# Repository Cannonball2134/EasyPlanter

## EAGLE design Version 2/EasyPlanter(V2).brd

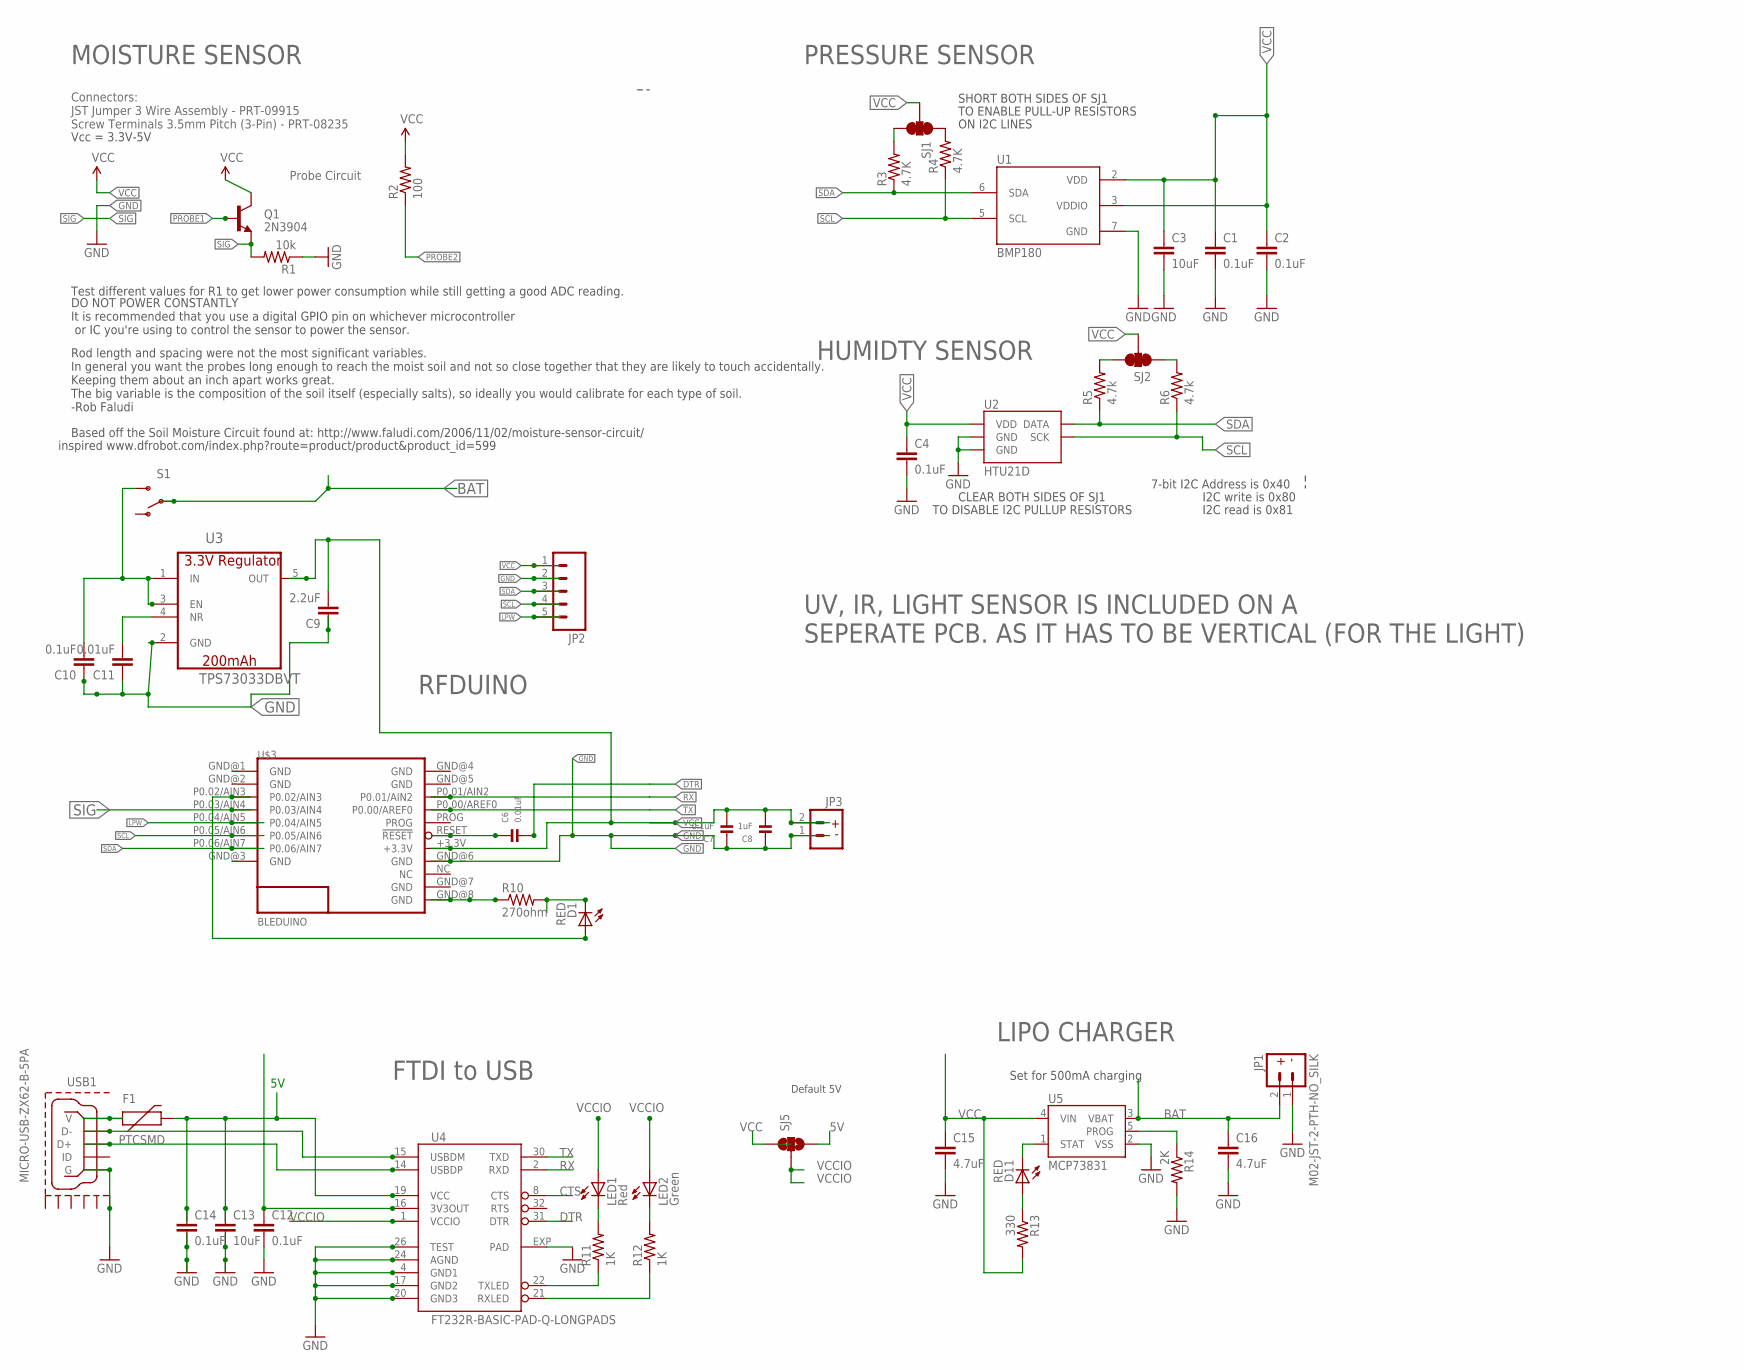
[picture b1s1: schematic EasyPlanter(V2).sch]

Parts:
C1, C2, C4: 0.1uF; 0603-CAP
C3: 10uF; 0603-CAP
C6: 0.01uF; 0402
C7: 0.1uF; 0402
C8: 1uF; 0402
C9: 2.2uF; 0402-CAP
C10, C12, C14: 0.1uF; 0402-CAP
C11: 0.01uF; 0402-CAP
C13: 10uF; 0402-CAP
C15, C16: 4.7uF; 0402-CAP
D1, D11: RED; LED-0603
F1: PTCSMD; PTC-1206
JP1, JP3: M02-JST-2-PTH-NO_SILK; JST-2-PTH-NS
JP2: M05PTH; 1X05
LED1: Red; LED-0603
LED2: Green; LED-0603
Q1: 2N3904; SOT23-3
R1: 10k; 0603-RES
R2: 100; 0603-RES
R3, R4: 4.7K; 0603-RES
R5, R6: 4.7k; 0603-RES
R10: 270ohm; 0402-RES
R11, R12: 1K; R0402
R13: 330; 0402-RES
R14: 2K; 0402-RES
S1: SWITCH-SPDT-SMD-A; SWITCH-SPST-SMD-A
SJ1, SJ2: SOLDERJUMPER_2WAYPASTE1&2&3; SJ_3_PASTE1&2&3
SJ5: SOLDERJUMPER_2WAY-LEFT-BRIDGED; SJ-3-LEFT
U1: BMP180
U2: HTU21D
U3: TPS73033DBVT; SOT95P290X145-5N
U4: FT232R-BASIC-PAD-Q-LONGPADS; QFN32-LONG
U5: MCP73831; SOT23-5
U$3: BLEDUINO
USB1: MICRO-USB-ZX62-B-5PA; ZX62-B-5PA

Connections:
5V: C13.1, C14.1, F1.2, SJ5.3, U4.19 (VCC)
BAT: C16.1, JP1.2, S1.2, U5.3 (VBAT)
BAT_INPUT: C10.2, S1.3 (S), U3.1 (IN), U3.3 (EN)
CTS: U4.8 (CTS)
DTR: C6.2, U4.31 (DTR)
GND: C1.2, C2.2, C3.2, C4.2, C7.1, C8.1, C9.1, C10.1, C11.1, C12.2, C13.2, C14.2, C15.2, C16.2, JP1.1, JP2.2, JP3.1, R1.1, R14.2, U1.7 (GND), U2.7 (GND), U2.GND, U3.2 (GND), U4.4 (GND1), U4.17 (GND2), U4.20 (GND3), U4.24 (AGND), U4.26 (TEST), U4.EXP (PAD), U5.2 (VSS), U$3.GND@6 (GND), USB1.5 (G), USB1.GND@6 (GND6)
GND1: USB1.GND@1 (GND1)
GND2: USB1.GND@2 (GND2)
GND3: USB1.GND@3 (GND3)
GND4: USB1.GND@4 (GND4)
GND5: USB1.GND@5 (GND5)
LPW: JP2.5, U$3.P0.04/AIN5
unnamed: R3.2, SJ1.3
unnamed: R4.2, SJ1.1
unnamed: R5.2, SJ2.3
unnamed: R6.2, SJ2.1
unnamed: C6.1, U$3.RESET (!RESET)
unnamed: D1.A, U$3.P0.02/AIN3
unnamed: C11.2, U3.4 (NR)
unnamed: U4.14 (USBDP), USB1.3 (D+)
unnamed: U4.15 (USBDM), USB1.2 (D-)
unnamed: R12.1, U4.21 (RXLED)
unnamed: R11.1, U4.22 (TXLED)
unnamed: F1.1, USB1.1 (V)
unnamed: LED1.C, R11.2
unnamed: LED2.C, R12.2
unnamed: D11.A, R13.1
unnamed: D1.C, R10.2
unnamed: R10.1, U$3.GND@8 (GND)
PROBE1: Q1.1 (B)
PROBE2: R2.1
PROG: R14.1, U5.5 (PROG)
RX: U4.2 (RXD), U$3.P0.01/AIN2
SCL: JP2.4, R4.1, R6.1, U1.5 (SCL), U2.SCK, U$3.P0.05/AIN6
SDA: JP2.3, R3.1, R5.1, U1.6 (SDA), U2.DATA, U$3.P0.06/AIN7
SIG: Q1.2 (E), R1.2, U$3.P0.03/AIN4
STAT: D11.C, U5.1 (STAT)
TX: U4.30 (TXD), U$3.P0.00/AREF0
VCC: C1.1, C2.1, C3.1, C4.1, C7.2, C8.2, C9.2, C12.1, C15.1, JP2.1, JP3.2, Q1.3 (C), R2.2, R13.2, SJ1.2, SJ2.2, SJ5.1, U1.2 (VDD), U1.3 (VDDIO), U2.VDD, U3.5 (OUT), U4.16 (3V3OUT), U5.4 (VIN), U$3.+3.3V
VCCIO: LED1.A, LED2.A, SJ5.2, U4.1 (VCCIO)

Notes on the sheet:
Test different values for R1 to get lower power consumption while still getting a good ADC reading.
Based off the Soil Moisture Circuit found at: http://www.faludi.com/2006/11/02/moisture-sensor-circuit/
Rod length and spacing were not the most significant variables. In general you want the probes long enough to reach the moist soil and not so close together that they are likely to touch accidentally. Keeping them about an inch apart works great. The big variable is the composition of the soil itse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
Connectors: JST Jumper 3 Wire Assembly - PRT-09915 Screw Terminals 3.5mm Pitch (3-Pin) - PRT-08235
Probe Circuit
Vcc = 3.3V-5V
DO NOT POWER CONSTANTLY It is recommended that you use a digital GPIO pin on whichever microcontroller or IC you're using to control the sensor to power the sensor.
inspired www.dfrobot.com/index.php?route=product/product&product_id=599
SHORT BOTH SIDES OF SJ1
TO ENABLE PULL-UP RESISTORS
ON I2C LINES
PRESSURE SENSOR
CLEAR BOTH SIDES OF SJ1
TO DISABLE I2C PULLUP RESISTORS
7-bit I2C Address is 0x40
I2C write is 0x80
I2C read is 0x81
HUMIDTY SENSOR
UV, IR, LIGHT SENSOR IS INCLUDED ON A SEPERATE PCB. AS IT HAS TO BE VERTICAL (FOR THE LIGHT)
MOISTURE SENSOR
Default 5V
VCCIO
FTDI to USB
RFDUINO
Set for 500mA charging
LIPO CHARGER

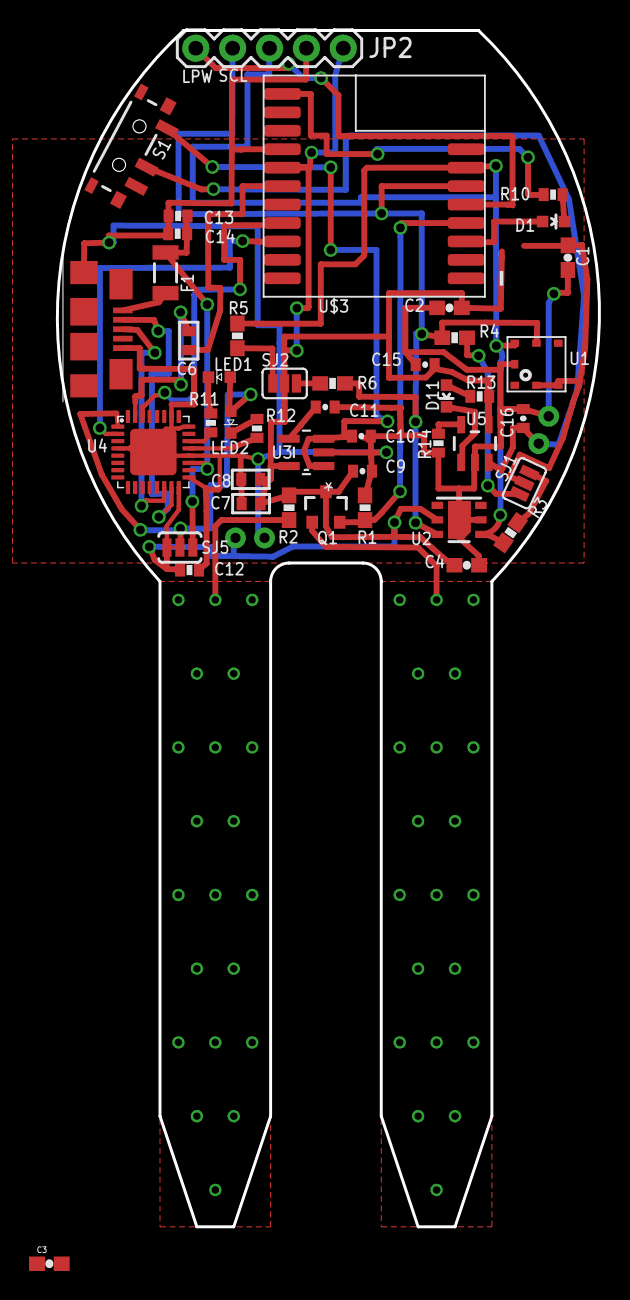
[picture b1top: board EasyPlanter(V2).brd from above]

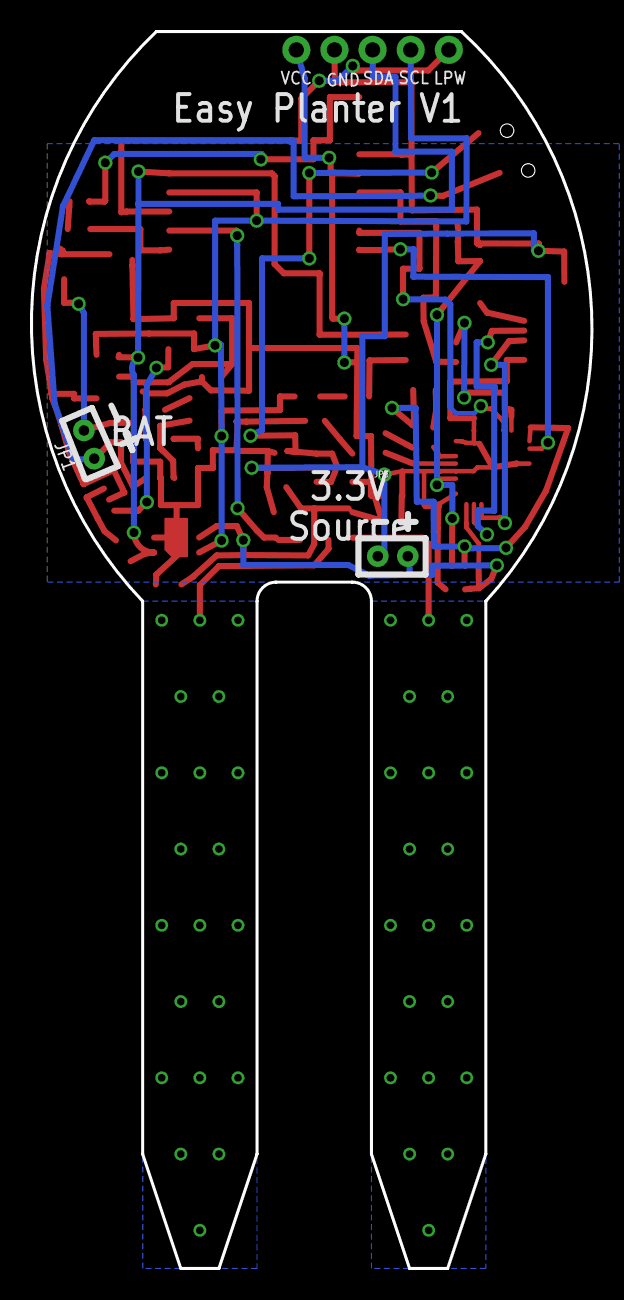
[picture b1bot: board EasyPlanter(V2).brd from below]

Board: 2 copper layers, 37.3 x 82.4 mm, 46 parts (2 on the bottom side), 32 nets.

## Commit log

2016-07-08 EasyPlanterV1
2016-07-10 Fix Tx Rx issue
    The TX and RX pins were the wrong way around.
2016-07-10 Version 2
    This is update to version 1 that fixes the RX & TX mix up

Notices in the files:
parts and their libraries:
SparkFun-DiscreteSemi: Licensing: Creative Commons ShareAlike 4.0 International - https://creativecommons.org/licenses/by-sa/4.0
SparkFun-Sensors: Licensing: CC v3.0 Share-Alike You are welcome to use this library for commercial purposes.
